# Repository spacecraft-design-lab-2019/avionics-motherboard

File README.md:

# avionics-motherboard
Main flight computer board for the PyCubed-1 spacecraft

Snapshot: 2019-10-24 maholli

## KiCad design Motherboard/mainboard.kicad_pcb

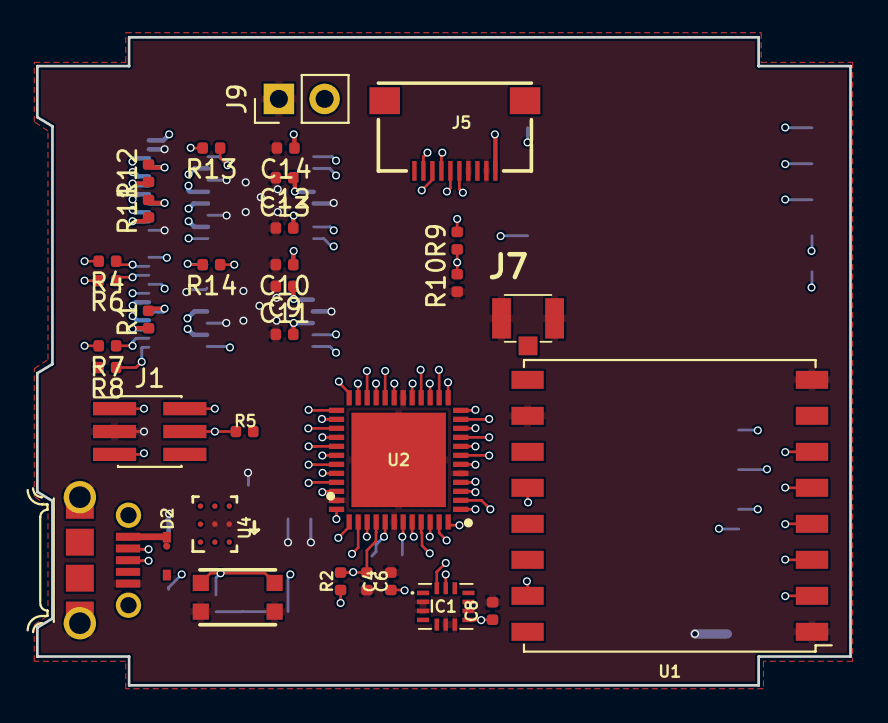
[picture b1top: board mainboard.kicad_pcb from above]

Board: 4 copper layers, 45.2 x 36.0 mm, 54 parts (0 on the bottom side), 60 nets.

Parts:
C1, C4, C8, C9, C12, C15, C16: 0.1uF; C_0402_1005Metric
C2, C7, C10, C14: 10uF; C_0402_1005Metric
C3, C5, C6: 1uF; C_0402_1005Metric
C11, C13: 2.2uF; C_0402_1005Metric
D2: RB550V; D_SOD-323
D3: WS2812B; LED_WS2812B_PLCC4_5.0x5.0mm_P3.2mm
FID1, FID2, FID3, FID4: Fiducial; Fiducial_1mm_Silkscreen
IC1: BMX160
J1: Conn_01x06; PinHeader_2x03_P1.27mm_Vertical_SMD
J2: 10118194-0001LF
J3: Micro_SD_Card; 503182-1853_MOLEX-MicroSD
J4: xf2m-2415-1a; XF2M-2415-1A
J5: XF2M-1015-1A
J6, J7: U.FL-R-SMT-1
J9: Conn_01x02; PinHeader_1x02_P2.54mm_Vertical
L1: 10uH; L_0805_2012Metric
R1, R11, R12: 0; R_0402_1005Metric
R2, R3, R4, R5, R6, R7, R8, R14: 10K; R_0402_1005Metric
R9, R10, R13: 100K; R_0402_1005Metric
SW1: KMR231NG LFS; BTN_KMR2_4.6X2.8
U1, U8: RFM95W-915S2; HOPERF_RFM9XW_SMD
U2: ATSAMD51G_TQFN48; QFN50P700X700X90-49N-D
U3, U5: DRV8848; SOP65P640X120-17N
U4: TPS82740BSIPR; TPS82740ASIPR
U6: MAX708RESA-T; SO-8_3.9x4.9mm_P1.27mm

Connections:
+3V3: C1.1, C3.1, C4.1, C7.1, C8.1, C11.2, C13.2, C15.1, C16.1, D3.1, IC1.5, IC1.8, IC1.12, J1.1, J3.4, J4.12, J4.13, R2.2, R4.2, R5.1, R6.2, R7.2, R8.2, R13.2, U1.13, U2.4, U2.6, U2.17, U2.36, U2.44, U3.11, U3.14, U4.C1, U5.11, U5.14, U6.2, U8.13
/SWCLK: J1.4, R5.2, U2.45
/SWDIO: J1.2, U2.46
/USB+: J2.3, U2.34
/USB-: J2.2, U2.33
BATTERY: R9.1, R10.2, U2.10
BATT_P: C9.1, C10.1, C12.1, C14.1, J4.24, J5.1, J9.2, R9.2, U3.12, U5.12
BATT_STATUS: J4.11, U2.27
BURN1: J4.7, U2.31
BURN2: J4.8, U2.29
COIL1_P: J4.22, U3.7
COIL2_N: J4.20, U3.5
COIL3_P: J4.18, U3.4
COIL4_N: J4.16, U3.2
COIL5_P: J4.6, U5.4
COIL6_N: J4.4, U5.2
CS_CAM: J5.9, U2.19
CS_SD: J3.2, U2.47
EN_CAM: J5.8, U2.16
GND: C1.2, C2.2, C3.2, C4.2, C5.2, C6.1, C7.2, C8.2, C9.2, C10.2, C11.1, C12.2, C13.1, C14.2, C15.2, C16.2, D3.3, IC1.2, IC1.3, IC1.6, IC1.7, J1.3, J2.5, J2.8, J2.9, J3.6, J3.SH1, J4.14, J4.23, J5.2, J5.4, J6.1, J6.2, J7.1, J7.2, J9.1, R10.1, SW1.B, SW1.B', U1.1, U1.8, U1.10, U2.5, U2.18, U2.35, U2.42, U2.49, U3.3, U3.6, U3.13, U3.17, U4.B2, U4.C2, U5.3, U5.6, U5.13, U5.17, U6.3, U6.4, U8.1, U8.8, U8.10
MINX_1: U2.23, U3.16
MINX_2: U2.22, U3.15
MINY_1: U2.24, U5.16
MINY_2: U2.32, U5.15
MINZ_1: U2.20, U3.9
MINZ_2: U2.21, U3.10
MISO: J3.7, J5.7, U1.2, U2.15, U8.2
MOSI: J3.3, J5.5, U1.3, U2.13, U8.3
M_EN: U2.28, U3.1, U5.1
M_FAULT: R13.1, R14.1, U2.30, U3.8
M_FAULT2: R14.2, U5.8
unnamed: C2.1, C5.1, L1.2, U2.41
unnamed: D2.1, U4.A1, U4.A2, U4.A3, U4.B3, U4.C3
unnamed: D3.4, U2.37
unnamed: J4.3, R1.1
unnamed: J4.5, R1.2
unnamed: J4.15, R11.1
unnamed: J4.17, R11.2
unnamed: J4.19, R12.1
unnamed: J4.21, R12.2
unnamed: J6.3, U8.9
unnamed: J7.3, U1.9
unnamed: L1.1, U2.43
unnamed: R3.2, U6.7, U6.8
RF1_BUSY: U2.11, U8.12
RF1_CS: U2.9, U8.5
RF1_IO1: U2.12, U8.15
RF1_RST: U2.8, U8.6
RF2_BUSY: U1.12, U2.39
RF2_CS: U1.5, U2.48
RF2_IO1: U1.15, U2.3
RF2_RST: U1.6, U2.7
SCK: J3.5, J5.6, U1.4, U2.14, U8.4
SCL1: IC1.13, J4.10, R4.1, U2.2
SCL2: J4.1, R8.1, U2.25
SDA1: IC1.14, J4.9, R6.1, U2.1
SDA2: J4.2, R7.1, U2.26
VUSB: D2.2, J2.1
WDT_WDI: U2.38, U6.6
~RESET: C6.2, J1.5, R2.1, R3.1, SW1.A, SW1.A', U2.40

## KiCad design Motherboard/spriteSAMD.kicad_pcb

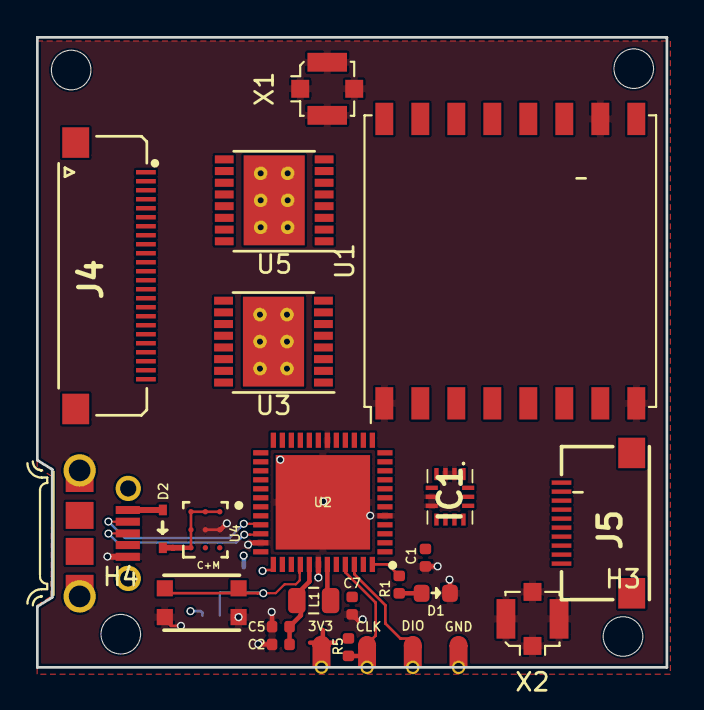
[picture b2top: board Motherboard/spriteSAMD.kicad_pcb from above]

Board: 4 copper layers, 35.0 x 35.0 mm, 34 parts (0 on the bottom side), 22 nets.

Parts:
C1: 0.1uF; C_0402_1005Metric
C2, C7: 10uF; C_0402_1005Metric
C3, C5, C6: 1uF; C_0402_1005Metric
D1: GREEN; LED_0603_1608Metric
D2: RB550V; D_SOD-323
H1, H2, H3, H4: MountingHole; MountingHole_2.2mm_M2
IC1: BMX160
J1, J28, J29, J30: Conn_01x01; castellated_small_1side
J2: 10118194-0001LF
J3: Micro_SD_Card; 503182-1853_MOLEX-MicroSD
J4: xf2m-2415-1a; XF2M-2415-1A
J5: XF2M-1015-1A
L1: 10uH; L_0805_2012Metric
R1: 330; R_0402_1005Metric
R2, R5: 10K; R_0402_1005Metric
SW1: KMR231NG LFS; BTN_KMR2_4.6X2.8
U1, U8: RFM95W-915S2; HOPERF_RFM9XW_SMD
U2: ATSAMD51G_TQFN48; QFN50P700X700X90-49N-D
U3, U5: DRV8833PWP; HTSSOP-16-1EP_4.4x5mm_P0.65mm_EP3.4x5mm_Mask2.46x2.31mm_The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
U4: TPS82740BSIPR; TPS82740ASIPR
X1, X2: ANTENNA_U.FL; U.FL_Molex_MCRF_73412-0110_Vertical

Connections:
+3V3: C1.1, C3.1, C7.1, IC1.5, IC1.8, J3.4, J29.1, R2.2, R5.1, U1.13, U2.4, U2.6, U2.17, U2.36, U2.44, U4.C1, U8.13
/LED1: R1.2, U2.48
/SWCLK: J28.1, R5.2, U2.45
/SWDIO: J1.1, U2.46
/USB+: J2.3, U2.34
/USB-: J2.2, U2.33
GND: C1.2, C2.2, C3.2, C5.2, C6.1, C7.2, D1.2, IC1.2, IC1.3, IC1.6, IC1.7, J2.5, J2.8, J2.9, J3.6, J30.1, SW1.B, SW1.B', U1.1, U1.8, U1.10, U2.5, U2.18, U2.35, U2.42, U2.49, U4.B2, U4.C2, U8.1, U8.8, U8.10, X1.1, X1.2, X2.1, X2.2
MISO: IC1.1, J3.7, U1.2, U2.15, U8.2
MOSI: IC1.14, J3.3, U1.3, U2.13, U8.3
unnamed: C2.1, C5.1, L1.2, U2.41
unnamed: C6.2, R2.1, SW1.A, SW1.A', U2.40
unnamed: D1.1, R1.1
unnamed: D2.1, U4.A1, U4.A2, U4.A3, U4.B3, U4.C3
unnamed: L1.1, U2.43
RF_BUSY: U2.1, U8.12
RF_DIO0: U2.47, U8.14
RF_DIO1: U2.39, U8.15
RF_DIO2: U2.38, U8.16
RF_DIO3: U2.2, U8.11
RF_RST: U2.21, U8.6
SCK: IC1.13, J3.5, U1.4, U2.14, U8.4
VUSB: D2.2, J2.1

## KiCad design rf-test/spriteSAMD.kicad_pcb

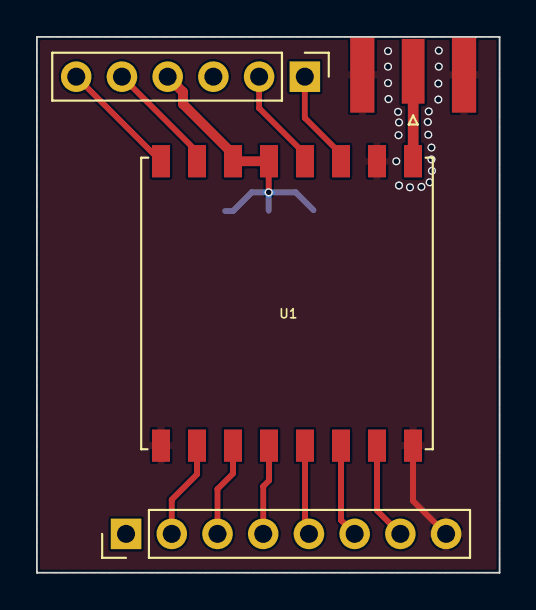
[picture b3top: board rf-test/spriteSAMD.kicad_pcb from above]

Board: 2 copper layers, 25.7 x 29.8 mm, 7 parts (0 on the bottom side), 13 nets.

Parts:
C1: 0.1uF; C_0402_1005Metric
C2: 1uF; C_0402_1005Metric
C3: 10uF; C_0402_1005Metric
J1: Conn_01x08_Female; PinHeader_1x08_P2.54mm_Vertical
J2: Conn_Coaxial; SMA_Samtec_SMA-J-P-H-ST-EM1_EdgeMount
J3: Conn_01x08_Female; PinHeader_1x06_P2.54mm_Vertical
U1: RFM95W-915S2; HOPERF_RFM9XW_SMD

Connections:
GND: C1.2, C2.2, C3.2, J1.8, J2.2, U1.1, U1.8, U1.10
MISO: J1.2, U1.2
MOSI: J1.3, U1.3
unnamed: J2.1, U1.9
P7: J1.7, U1.7
RF_BUSY: J3.2, U1.12
RF_CS: J1.5, U1.5
RF_DIO0: C1.1, C2.1, C3.1, J3.4, U1.13, U1.14
RF_DIO1: J3.5, U1.15
RF_DIO2: J3.6, U1.16
RF_DIO3: J3.1, U1.11
RF_RST: J1.6, U1.6
SCK: J1.4, U1.4

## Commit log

2019-10-19 the will-it-all-fit test... ✔
2019-10-19 if I fits... 😺
2019-10-19 added WDT and took closer-look at fit
2019-10-19 labeled schematic in case anyone ends up seeing this
2019-10-20 changed KiCad project name and fixed linking
2019-10-21 deleted battery connector (should be apart of 24-pin FPC)
2019-10-21 Motherboard files 10/21/2019
    Added Hbridge circuit, also added netlabels for camera connector
2019-10-24 branching for fabrication clean-up and review
2019-10-24 placement clean-up
2019-10-24 placement getting closer
2019-10-24 placement roughed-in & routing planned
2019-10-24 rearranging for power distrobution
2019-10-24 much cleaner SPI and BATT_P layout
2019-10-24 ~75% routed
2019-10-24 routing ~80%
2019-10-24 routed except for connectors
2019-10-24 changed IMU from SPI to I2C for pins
2019-10-24 lots of clean up
2019-10-24 putting matching coils in series
2019-10-24 coil bridges with contingency finished
2019-10-24 big FPC routed
2019-10-24 neopixel 🚥
2019-10-24 adding pdf of schematic
2019-10-24 snapshot for readme
2019-10-24 relative path for readme snapshot
2019-10-25 100% routed
2019-10-25 finished- might fiddle with later
2019-10-26 fab files for max version of MB
2019-10-26 JLCPCB fab output
2019-10-26 interactive BOM
2019-10-27 rftest ready for fab
2019-10-28 generating 3D CAD
2019-10-29 adding mainboard_max step
2019-11-01 stencil outputs
2022-02-24 Fix typo in README.md

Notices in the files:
parts and their libraries:
Copyright 2016 Accelerated Designs. All rights reserved.
